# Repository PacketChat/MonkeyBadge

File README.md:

# Monkey Badge

This repository contains the hardware design files, badge code, and backend
infrastructure code for the HushCon Winter 2023 badge.

## badge

The code for the badge is based on [Micropython][1].  For full documentation
read the datasheet, comments, and commit history.

## api-server

The api-server is the backend gameserver it provides an API
interface for the badge to save state and complete challenges.

You will need a redis server with the json mod, `docker run -d -p 6379:6379
redislabs/redismod` works fine.

This is based on FastAPI and is easily executed with: `cd api-server; python3
api-server`

## scoreboard

Built, with Flask

<!--
vim: ts=2 sw=2 tw=80 syntax=md
!-->

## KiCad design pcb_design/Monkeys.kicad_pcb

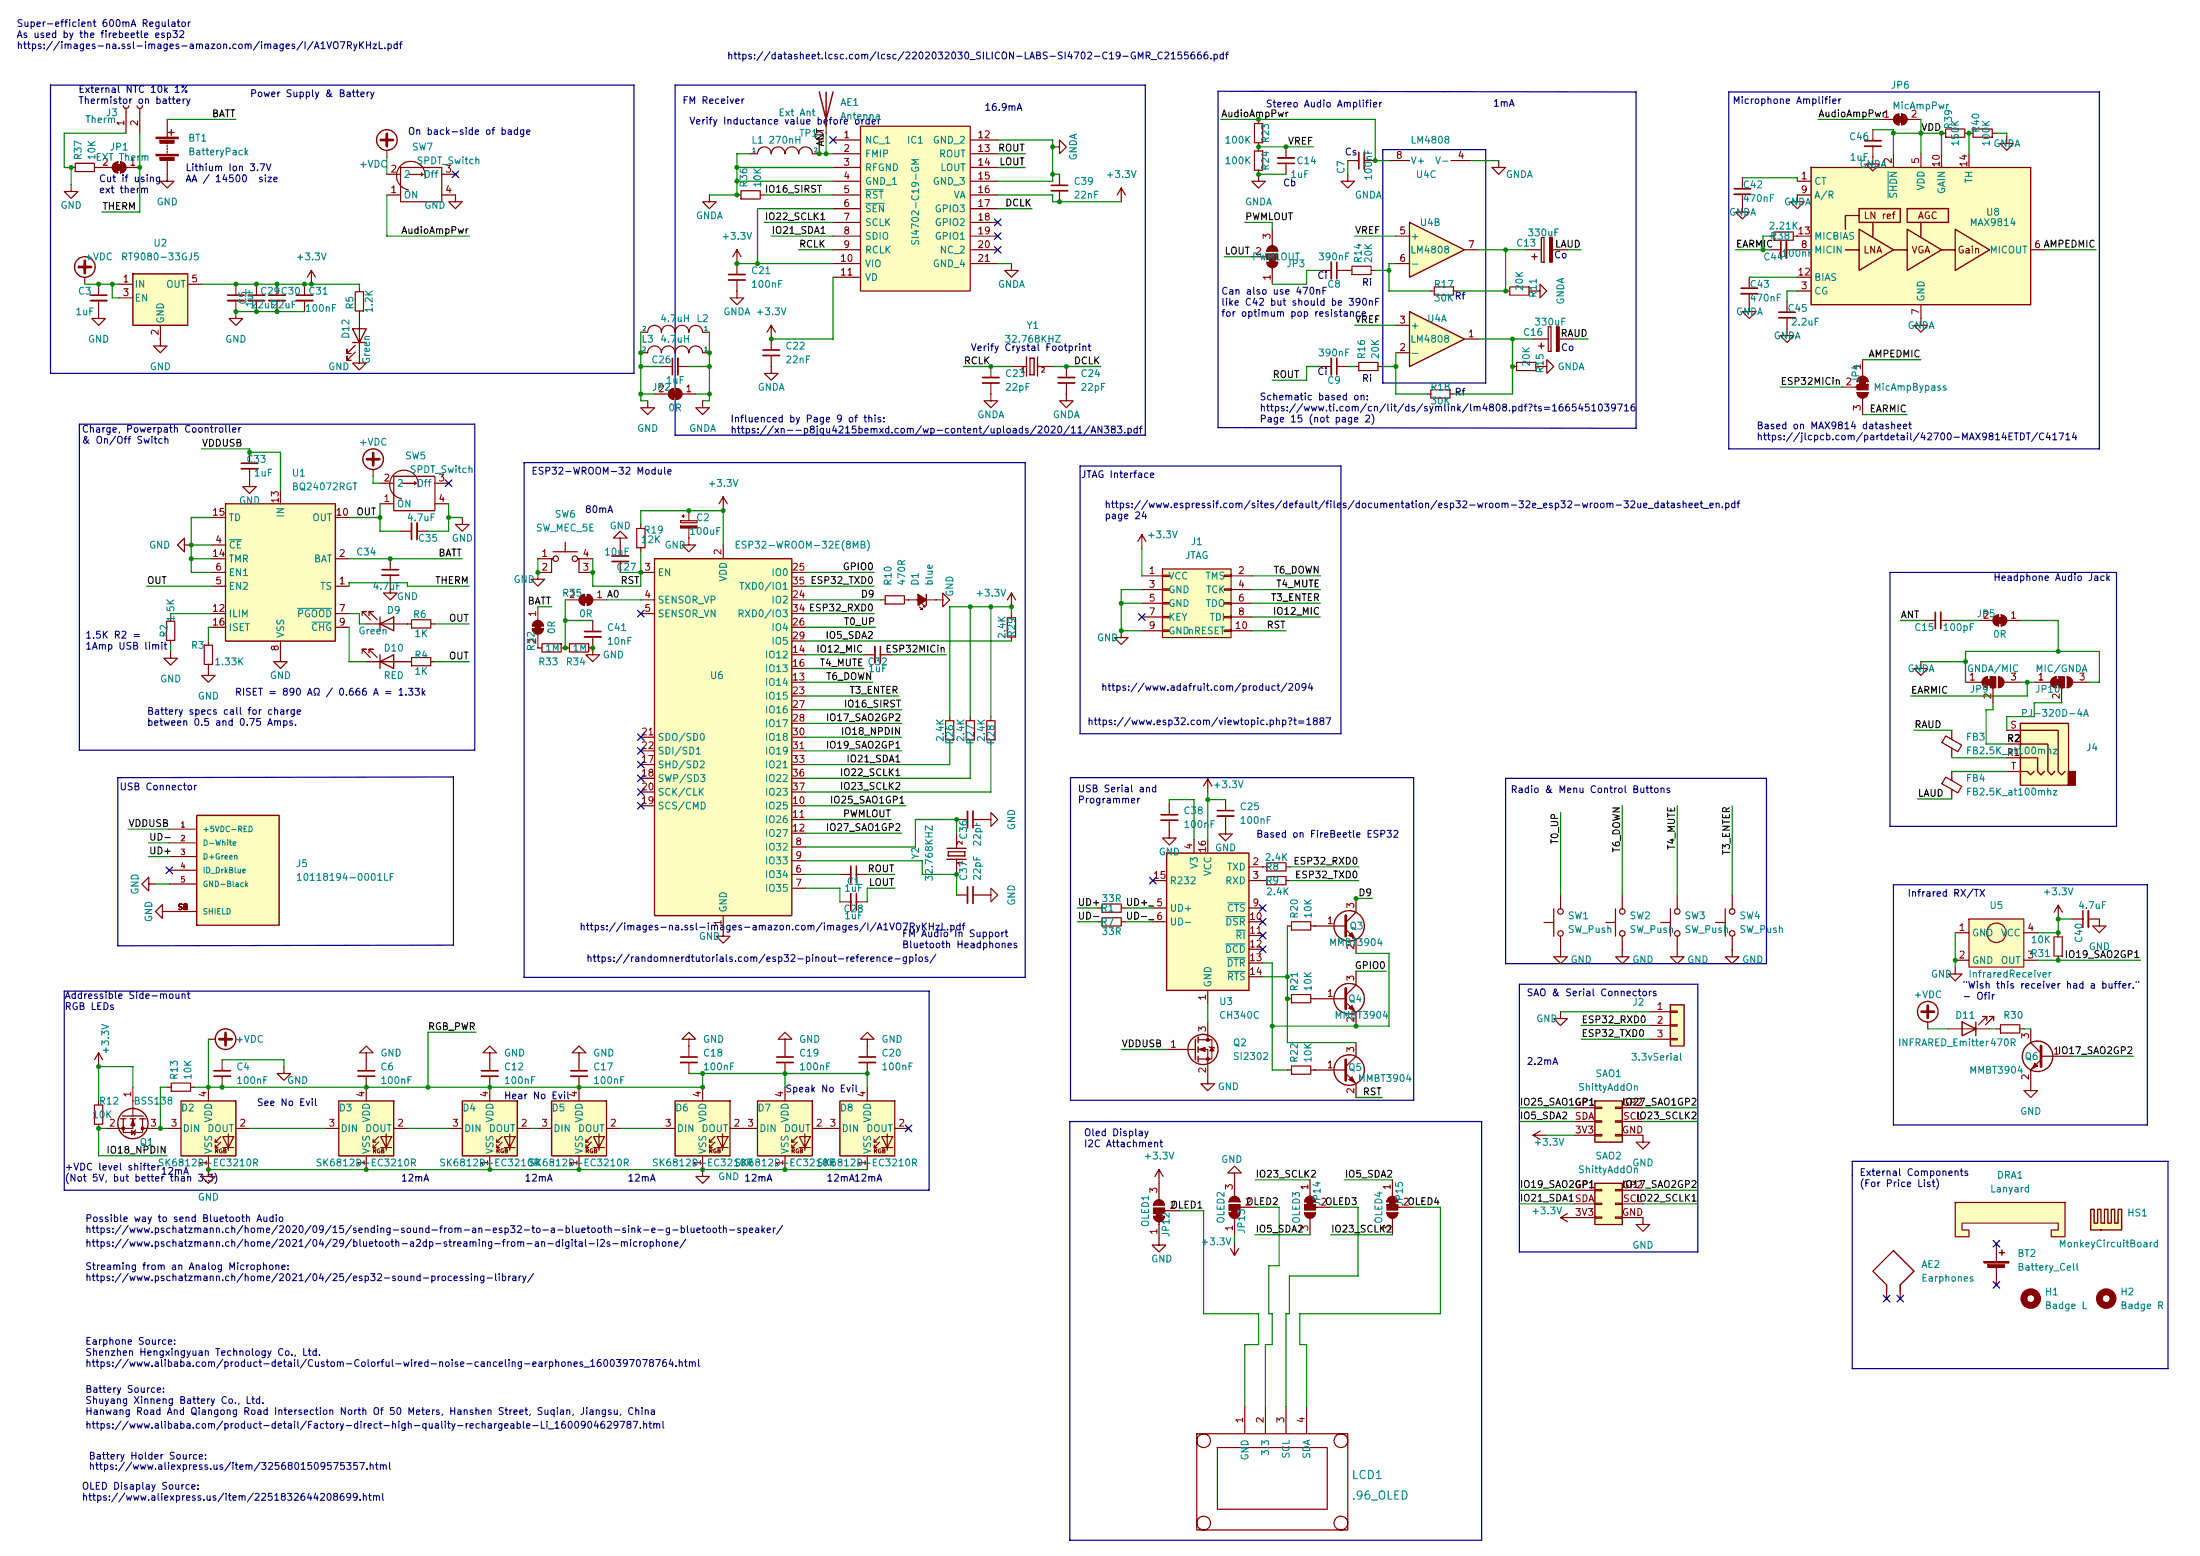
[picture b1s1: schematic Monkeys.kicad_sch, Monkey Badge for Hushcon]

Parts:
AE1: Antenna; Manufacturer_Part_Number DNP; JLCPCB Part #（optional) DNP
AE2: Earphones; Manufacturer_Part_Number DNP; JLCPCB Part #（optional) DNP
BT1: BatteryPack; 1xAA_NUB; Manufacturer_Part_Number DNP; JLCPCB Part #（optional) DNP
BT2: Battery_Cell; Manufacturer_Part_Number DNP; JLCPCB Part #（optional) DNP
C1, C3, C5, C14, C26, C28, C32, C46: 1uF; C_0402_1005Metric; Manufacturer_Part_Number CC0402KRX5R6BB105; JLCPCB Part #（optional) C106254
C2: 100uF; CP_EIA-6032-20_AVX-F; Manufacturer_Part_Number TAJC107K010RNJ; JLCPCB Part #（optional) C8649
C4, C6, C7, C12, C17, C18, C19, C20, C21, C25, C31, C38, C44: 100nF; C_0402_1005Metric; Manufacturer_Part_Number CL05B104KB54PNC; JLCPCB Part #（optional) C307331
C8, C9: 390nF; C_0402_1005Metric; Manufacturer_Part_Number GRM155R61A394KE15D; JLCPCB Part #（optional) C350937
C13, C16: 330uF; CP_EIA-7343-31_Kemet-D; Manufacturer_Part_Number 6TPC330MA; JLCPCB Part #（optional) C558795
C15: 100pF; C_0402_1005Metric; Manufacturer_Part_Number 0402CG101J500NT; JLCPCB Part #（optional) C1546
C22, C39: 22nF; C_0402_1005Metric; Manufacturer_Part_Number 0402B223K500NT; JLCPCB Part #（optional) C1532
C23, C24, C36, C37: 22pF; C_0402_1005Metric; Manufacturer_Part_Number 0402CG220J500NT; JLCPCB Part #（optional) C1555
C27: 10uF; C_0603_1608Metric; Manufacturer_Part_Number CL10A106KP8NNNC; JLCPCB Part #（optional) C19702
C29, C30: 22uF; C_0805_2012Metric; Manufacturer_Part_Number CL21A226MAQNNNE; JLCPCB Part #（optional) C45783
C33: 1uF; C_0805_2012Metric; Manufacturer_Part_Number CC0805KKX7R8BB105; JLCPCB Part #（optional) C91186
C34, C35, C40: 4.7uF; C_0603_1608Metric; Manufacturer_Part_Number CC0603KRX5R6BB475; JLCPCB Part #（optional) C109456
C41: 10nF; C_0402_1005Metric; Manufacturer_Part_Number CL05B103KB5NNNC; JLCPCB Part #（optional) C15195
C42, C43: 470nF; C_0402_1005Metric; Manufacturer_Part_Number C1005X5R474KDTS; JLCPCB Part #（optional) C147712
C45: 2.2uF; C_0402_1005Metric; Manufacturer_Part_Number LMK105ABJ225MVHF; JLCPCB Part #（optional) C386041
D1: blue; LED_0402_1005Metric; Manufacturer_Part_Number TJ-S1005SW4TGLC6B-A5; JLCPCB Part #（optional) C273603
D2, D3, D4, D5, D6, D7, D8: SK6812D-EC3210R; Manufacturer_Part_Number SK6812D-EC3210R; JLCPCB Part #（optional) C2890041
D9, D12: Green; LED_0805_2012Metric; Manufacturer_Part_Number 17-215SYGC/S530-E2/TR8; JLCPCB Part #（optional) C282125
D10: RED; LED_0603_1608Metric; Manufacturer_Part_Number KT-0603R; JLCPCB Part #（optional) C2286
D11: INFRARED_Emitter; LED_1206_3216Metric; Manufacturer_Part_Number MHT153IRCT; JLCPCB Part #（optional) C2764887
DRA1: Lanyard; DNP; Manufacturer_Part_Number DNP; JLCPCB Part #（optional) DNP
FB3, FB4: FB2.5K_at100mhz; C_0603_1608Metric; Manufacturer_Part_Number SZ1608K252CTF; JLCPCB Part #（optional) C316340
H1: Badge L; MountingHole_4.5mm; Manufacturer_Part_Number DNP; JLCPCB Part #（optional) DNP
H2: Badge R; MountingHole_4.5mm; Manufacturer_Part_Number DNP; JLCPCB Part #（optional) DNP
HS1: MonkeyCircuitBoard; DNP; Manufacturer_Part_Number DNP; JLCPCB Part #（optional) DNP
IC1: SI4702-C19-GM; SI4702C19GM; Manufacturer_Part_Number SI4702-C19-GM; JLCPCB Part #（optional) C2155666
J1: JTAG; PinHeader_2x05_P1.27mm_Vertical; Manufacturer_Part_Number DNP; JLCPCB Part #（optional) DNP
J2: 3.3vSerial; PinSocket_1x03_P2.54mm_Vertical; Manufacturer_Part_Number DNP; JLCPCB Part #（optional) DNP
J3: Therm; PinHeader_1x02_P2.54mm_Vertical; Manufacturer_Part_Number DNP; JLCPCB Part #（optional) DNP
J4: PJ-320D-4A; Jack_3.5mm_PJ320D_Horizontal; Manufacturer_Part_Number PJ-320D-4A; JLCPCB Part #（optional) C95562
J5: 10118194-0001LF; AMPHENOL_10118194-0001LF_JT; Manufacturer_Part_Number 10118194-0001LF; JLCPCB Part #（optional) C132563
JP1: EXT Therm; SolderJumper-2_P1.3mm_Bridged_RoundedPad1.0x1.5mm; Manufacturer_Part_Number DNP; JLCPCB Part #（optional) DNP
JP2, JP5: 0R; SolderJumper-2_P1.3mm_Bridged_RoundedPad1.0x1.5mm; Manufacturer_Part_Number DNP; JLCPCB Part #（optional) DNP
JP3: PWMLOUT; SolderJumper-3_P1.3mm_Bridged12_RoundedPad1.0x1.5mm; Manufacturer_Part_Number DNP; JLCPCB Part #（optional) DNP
JP4: MicAmpBypass; SolderJumper-3_P1.3mm_Bridged12_RoundedPad1.0x1.5mm; Manufacturer_Part_Number DNP; JLCPCB Part #（optional) DNP
JP6: MicAmpPwr; SolderJumper-2_P1.3mm_Bridged_RoundedPad1.0x1.5mm
JP9: GNDA/MIC; SolderJumper-3_P1.3mm_Bridged12_RoundedPad1.0x1.5mm; Manufacturer_Part_Number DNP; JLCPCB Part #（optional) DNP
JP10: MIC/GNDA; SolderJumper-3_P1.3mm_Bridged12_RoundedPad1.0x1.5mm; Manufacturer_Part_Number DNP; JLCPCB Part #（optional) DNP
JP12: OLED1; SolderJumper-3_P1.3mm_Bridged12_RoundedPad1.0x1.5mm; Manufacturer_Part_Number DNP; JLCPCB Part #（optional) DNP
JP13: OLED2; SolderJumper-3_P1.3mm_Bridged12_RoundedPad1.0x1.5mm; Manufacturer_Part_Number DNP; JLCPCB Part #（optional) DNP
JP14: OLED3; SolderJumper-3_P1.3mm_Bridged12_RoundedPad1.0x1.5mm; Manufacturer_Part_Number DNP; JLCPCB Part #（optional) DNP
JP15: OLED4; SolderJumper-3_P1.3mm_Bridged12_RoundedPad1.0x1.5mm; Manufacturer_Part_Number DNP; JLCPCB Part #（optional) DNP
L1: 270nH; L_0603_1608Metric_Pad1.05x0.95mm_HandSolder; Manufacturer_Part_Number SCHF160808HR27JT; JLCPCB Part #（optional) C578010
L2, L3: 4.7uH; L_0603_1608Metric_Pad1.05x0.95mm_HandSolder; Manufacturer_Part_Number MLP2012S4R7MT0S1; JLCPCB Part #（optional) C87543
LCD1: .96_OLED; PinHeader_1x04_P2.54mm_Vertical; Manufacturer_Part_Number DNP; JLCPCB Part #（optional) DNP
Q1: BSS138; SOT-323_SC-70; Manufacturer_Part_Number BSS138W-7-F; JLCPCB Part #（optional) C24553
Q2: SI2302; SOT-23; Manufacturer_Part_Number SI2302; JLCPCB Part #（optional) C351399
Q3, Q4, Q5, Q6: MMBT3904; SOT-23; Manufacturer_Part_Number MMBT3904; JLCPCB Part #（optional) C20526
R1, R7: 33R; R_0402_1005Metric; Manufacturer_Part_Number 0402WGF330JTCE; JLCPCB Part #（optional) C25105
R2: 1.5K; R_0805_2012Metric; Manufacturer_Part_Number RC0805FR-071K5L; JLCPCB Part #（optional) C114555
R3: 1.33K; R_0603_1608Metric; Manufacturer_Part_Number RC0603FR-071K33L; JLCPCB Part #（optional) C137778
R4, R6: 1K; R_0805_2012Metric; Manufacturer_Part_Number RC0805JR-071KL; JLCPCB Part #（optional) C100046
R5: 1.2K; R_0805_2012Metric; Manufacturer_Part_Number AR05FTDW1201; JLCPCB Part #（optional) C724883
R8, R9, R26, R27, R28, R29: 2.4K; R_0603_1608Metric; Manufacturer_Part_Number RC0603FR-072K4L; JLCPCB Part #（optional) C114611
R10, R30: 470R; R_0402_1005Metric; Manufacturer_Part_Number 0402WGF4700TCE; JLCPCB Part #（optional) C25117
R11, R14, R15, R16: 20K; R_0402_1005Metric; Manufacturer_Part_Number 0402WGF2002TCE; JLCPCB Part #（optional) C25765
R12, R13, R20, R21, R22, R31, R36, R37: 10K; R_0402_1005Metric; Manufacturer_Part_Number RC0402FR-0710KL; JLCPCB Part #（optional) C60490
R17, R18: 30K; R_0402_1005Metric; Manufacturer_Part_Number RC0402FR-0730KL; JLCPCB Part #（optional) C138008
R19: 12K; R_0402_1005Metric; Manufacturer_Part_Number RC0402FR-0712KL; JLCPCB Part #（optional) C114760
R23, R24, R40: 100K; R_0402_1005Metric; Manufacturer_Part_Number 0402WGF1003TCE; JLCPCB Part #（optional) C25741
R32, R35: 0R; SolderJumper-2_P1.3mm_Bridged_RoundedPad1.0x1.5mm; Manufacturer_Part_Number DNP; JLCPCB Part #（optional) DNP
R33, R34: 1M; R_0402_1005Metric; Manufacturer_Part_Number 0402WGF1004TCE; JLCPCB Part #（optional) C26083
R38: 2.21K; R_0402_1005Metric; Manufacturer_Part_Number NQ02WGF2211TCE; JLCPCB Part #（optional) C270376
R39: 150K; R_0402_1005Metric; Manufacturer_Part_Number AF0402FR-07150KL; JLCPCB Part #（optional) C144033
SAO1, SAO2: ShittyAddOn; ShittyAddOn_Female; Manufacturer_Part_Number DNP; JLCPCB Part #（optional) DNP
SW1, SW2, SW3, SW4: SW_Push; SW_SPST_PTS645; Manufacturer_Part_Number TSA063G50-250; JLCPCB Part #（optional) C294565
SW5, SW7: SPDT_Switch; SPDT Switch MSK12C02-HB; Manufacturer_Part_Number MSK12C02-HB; JLCPCB Part #（optional) C431541
SW6: SW_MEC_5E; Button_metal; Manufacturer_Part_Number TS-1187A-B-A-B; JLCPCB Part #（optional) C318884
TP1: Ext Ant; PinHeader_1x01_P2.54mm_Vertical; Manufacturer_Part_Number DNP; JLCPCB Part #（optional) DNP
U1: BQ24072RGT; VQFN-16-1EP_3x3mm_P0.5mm_EP1.6x1.6mm; Manufacturer_Part_Number BQ24072RGTR; JLCPCB Part #（optional) C140288
U2: RT9080-33GJ5; SOT-23-5; Manufacturer_Part_Number RT9080-33GJ5; JLCPCB Part #（optional) C841192
U3: CH340C; SOIC-16_3.9x9.9mm_P1.27mm; Manufacturer_Part_Number CH340C; JLCPCB Part #（optional) C84681
U4: LM4808; SOIC-8_3.9x4.9mm_P1.27mm; Manufacturer_Part_Number LM4808MX/NOPB; JLCPCB Part #（optional) C141374
U5: InfraredReceiver; IRM-H638T-TR2; Manufacturer_Part_Number IRM-H638T/TR2(DX); JLCPCB Part #（optional) C390031
U6: ESP32-WROOM-32E(8MB); ESP32-WROOM-32; Manufacturer_Part_Number ESP32-WROOM-32E(8MB); JLCPCB Part #（optional) C701342
U8: MAX9814; DFN-14-1EP_3x3mm_P0.4mm_EP1.78x2.35mm; Manufacturer_Part_Number MAX9814ETD+T; JLCPCB Part #（optional) C41714
Y1, Y2: 32.768KHZ; Crystal_SMD_3215-2Pin_3.2x1.5mm; Manufacturer_Part_Number SF32WK32768D31T002; JLCPCB Part #（optional) C271654

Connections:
+3V3: C2.1, C5.1, C21.1, C22.1, C25.1, C29.1, C30.1, C31.1, C39.2, C40.1, IC1.6 (~SEN), IC1.10 (VIO), IC1.11 (VD), IC1.16 (VA), J1.1 (VCC), JP12.3 (B), JP13.1 (A), Q1.1 (G), R5.2, R12.2, R19.2, R26.2, R27.2, R28.2, R29.2, R31.2, SAO1.3V3, SAO2.3V3, U2.5 (OUT), U3.16 (VCC), U5.4 (VCC), U6.2 (VDD)
+VDC: C3.1, C4.2, C6.2, C12.2, C17.2, C18.2, C19.2, C20.2, D2.4 (VDD), D3.4 (VDD), D4.4 (VDD), D5.4 (VDD), D6.4 (VDD), D7.4 (VDD), D8.4 (VDD), D11.2 (A), R13.2, SW5.2, SW7.2, U2.1 (IN), U2.3 (EN)
/A0: R35.1 (A), U6.4 (SENSOR_VP)
/AMPEDMIC: JP4.1 (A), U8.6 (MICOUT)
/ANT: AE1.1, C15.1, IC1.2 (FMIP), L1.2, TP1.1
/AudioAmpPwr: C7.2, JP6.1 (A), R23.1, SW7.1 (ON), U4.8 (V+)
/BATT: BT1.1 (+), C34.1, R32.1 (A), U1.2 (BAT), U1.3 (BAT)
/D9: Q3.3 (C), R10.1, U6.24 (IO2)
/DCLK: C24.1, IC1.17 (GPIO3), Y1.2
/EARMIC: C44.1, JP4.3 (B), JP9.3 (B), JP10.1 (A), R38.1
/ESP32MICin: C32.1, JP4.2 (C)
/ESP32_RXD0: J2.2, R8.2, U6.34 (RXD0/IO3)
/ESP32_TXD0: J2.3, R9.2, U6.35 (TXD0/IO1)
/GPIO0: Q4.3 (C), U6.25 (IO0)
/IO5_SDA2: JP14.3 (B), JP15.1 (A), R29.1, SAO1.SDA, U6.29 (IO5)
/IO12_MIC: C32.2, J1.8 (TDI), U6.14 (IO12)
/IO16_SIRST: IC1.5 (~RST), R36.2, U6.27 (IO16)
/IO17_SAO2GP2: Q6.1 (B), SAO2.GP2 (GPIO2), U6.28 (IO17)
/IO18_NPDIN: Q1.2 (S), R12.1, U6.30 (IO18)
/IO19_SAO2GP1: R31.1, SAO2.GP1 (GPIO1), U5.3 (OUT), U6.31 (IO19)
/IO21_SDA1: IC1.8 (SDIO), R26.1, SAO2.SDA, U6.33 (IO21)
/IO22_SCLK1: IC1.7 (SCLK), R27.1, SAO2.SCL, U6.36 (IO22)
/IO23_SCLK2: JP14.1 (A), JP15.3 (B), R28.1, SAO1.SCL, U6.37 (IO23)
/IO25_SAO1GP1: SAO1.GP1 (GPIO1), U6.10 (IO25)
/IO27_SAO1GP2: SAO1.GP2 (GPIO2), U6.12 (IO27)
/LAUD: C13.2, FB4.2
/LOUT: C28.1, IC1.14 (LOUT), JP3.2 (C)
/OLED1: JP12.2 (C), LCD1.1 (GND)
/OLED2: JP13.2 (C), LCD1.2 (3.3)
/OLED3: JP14.2 (C), LCD1.3 (SCL)
/OLED4: JP15.2 (C), LCD1.4 (SDA)
/OUT: C35.1, R4.2, R6.2, SW5.1 (ON), U1.5 (EN2), U1.10 (OUT), U1.11 (OUT)
/PWMLOUT: JP3.3 (B), U6.11 (IO26)
/R2: J4.R2, JP9.2 (C)
/RAUD: C16.2, FB3.1
/RCLK: C23.1, IC1.9 (RCLK), Y1.1
/ROUT: C1.1, C9.2, IC1.13 (ROUT)
/RST: C27.1, J1.10 (nRESET), Q5.2 (E), R19.1, SW6.3 (K), SW6.4 (A), U6.3 (EN)
/T0_UP: SW1.2, U6.26 (IO4)
/T3_ENTER: J1.6 (TDO), SW4.2, U6.23 (IO15)
/T4_MUTE: J1.4 (TCK), SW3.2, U6.16 (IO13)
/T6_DOWN: J1.2 (TMS), SW2.2, U6.13 (IO14)
/THERM: J3.2, JP1.1 (A), U1.1 (TS)
/UD+: J5.3 (D+Green), R1.1
/UD+_: R1.2, U3.5 (UD+)
/UD-: J5.2 (D-White), R7.1
/UD-_: R7.2, U3.6 (UD-)
/VDD: C46.1, JP6.2 (B), R39.1, U8.2 (~SHDN), U8.5 (VDD), U8.10 (GAIN)
/VDDUSB: C33.1, J5.1 (+5VDC-RED), Q2.1 (G), U1.13 (IN)
/VREF: C14.2, R23.2, R24.1, U4.3 (+), U4.5 (+)
GND: BT1.2 (-), C2.2, C3.2, C4.1, C5.2, C6.1, C12.1, C17.1, C18.1, C19.1, C20.1, C25.2, C26.1, C27.2, C29.2, C30.2, C31.2, C33.2, C34.2, C35.2, C36.2, C37.2, C38.2, C40.2, C41.2, D1.1 (K), D2.1 (VSS), D3.1 (VSS), D4.1 (VSS), D5.1 (VSS), D6.1 (VSS), D7.1 (VSS), D8.1 (VSS), D12.1 (K), J1.3 (GND), J1.5 (GND), J1.9 (GND), J2.1, J3.1, J5.5 (GND-Black), J5.S1 (SHIELD), J5.S2 (SHIELD), J5.S3 (SHIELD), J5.S4 (SHIELD), J5.S5 (SHIELD), J5.S6 (SHIELD), JP2.2 (B), JP12.1 (A), JP13.3 (B), L2.2, L3.2, Q2.2 (S), Q6.2 (E), R2.1, R3.2, R34.1, R37.1, SAO1.GND, SAO2.GND, SW1.1, SW2.1, SW3.1, SW4.1, SW5.4, SW6.1, SW6.2, SW7.4, U1.4 (~CE), U1.6 (EN1), U1.8 (VSS), U1.14 (TMR), U1.15 (TD), U1.17 (VSS), U2.2 (GND), U5.1 (GND), U5.2 (GND), U6.1 (GND), U6.15 (GND), U6.38 (GND), U6.39 (GND)
GNDA: C7.1, C14.1, C21.2, C22.2, C23.2, C24.2, C26.2, C39.1, C42.2, C43.2, C45.2, C46.2, IC1.3 (RFGND), IC1.4 (GND_1), IC1.12 (GND_2), IC1.15 (GND_3), IC1.21 (GND_4), JP2.1 (A), JP5.1 (A), JP9.1 (A), JP10.3 (B), L1.1, L2.1, L3.1, R11.1, R15.1, R24.2, R36.1, R40.1, U4.4 (V-), U8.4 (GND), U8.7 (GND), U8.9 (A/R), U8.11 (GND), U8.15 (GND)
unnamed: C1.2, U6.6 (IO34)
unnamed: C8.1, R14.1
unnamed: C8.2, JP3.1 (A)
unnamed: C9.1, R16.1
unnamed: C13.1, R11.2, R17.1, U4.7
unnamed: C15.2, JP5.2 (B)
unnamed: C16.1, R15.2, R18.1, U4.1
unnamed: C28.2, U6.7 (IO35)
unnamed: C36.1, U6.8 (IO32), Y2.2
unnamed: C37.1, U6.9 (IO33), Y2.1
unnamed: C38.1, U3.4 (V3)
unnamed: C41.1, R33.1, R34.2, R35.2 (B)
unnamed: C42.1, U8.1 (CT)
unnamed: C43.1, U8.12 (BIAS)
unnamed: C44.2, U8.8 (MICIN)
unnamed: C45.1, U8.3 (CG)
unnamed: D1.2 (A), R10.2
unnamed: D2.2 (DOUT), D3.3 (DIN)
unnamed: D2.3 (DIN), Q1.3 (D), R13.1
unnamed: D3.2 (DOUT), D4.3 (DIN)
unnamed: D4.2 (DOUT), D5.3 (DIN)
unnamed: D5.2 (DOUT), D6.3 (DIN)
unnamed: D6.2 (DOUT), D7.3 (DIN)
unnamed: D7.2 (DOUT), D8.3 (DIN)
unnamed: D9.1 (K), U1.7 (~PGOOD)
unnamed: D9.2 (A), R6.1
unnamed: D10.1 (K), U1.9 (~CHG)
unnamed: D10.2 (A), R4.1
unnamed: D11.1 (K), R30.1
unnamed: D12.2 (A), R5.1
unnamed: FB3.2, J4.R1
unnamed: FB4.1, J4.T
unnamed: J4.S, JP10.2 (C)
unnamed: JP1.2 (B), R37.2
unnamed: Q2.3 (D), U3.1 (GND)
unnamed: Q3.1 (B), R20.2
unnamed: Q3.2 (E), Q4.2 (E), R22.1, U3.13 (~DTR)
unnamed: Q4.1 (B), R21.2
unnamed: Q5.1 (B), R22.2
unnamed: Q5.3 (C), R20.1, R21.1, U3.14 (~RTS)
unnamed: Q6.3 (C), R30.2
unnamed: R2.2, U1.12 (ILIM)
unnamed: R3.1, U1.16 (ISET)
unnamed: R8.1, U3.2 (TXD)
unnamed: R9.1, U3.3 (RXD)
unnamed: R14.2, R17.2, U4.6 (-)
unnamed: R16.2, R18.2, U4.2 (-)
unnamed: R32.2 (B), R33.2
unnamed: R38.2, U8.13 (MICBIAS)
unnamed: R39.2, R40.2, U8.14 (TH)

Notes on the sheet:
See No Evil
Can also use 470nF like C42 but should be 390nF for optimum pop resistance
https://www.alibaba.com/product-detail/Factory-direct-high-quality-rechargeable-Li_1600904629787.html
Addressible Side-mount RGB LEDs
Battery specs call for charge between 0.5 and 0.75 Amps.
https://www.aliexpress.us/item/3256801509575357.html
12mA
Speak No Evil
https://datasheet.lcsc.com/lcsc/2202032030_SILICON-LABS-SI4702-C19-GMR_C2155666.pdf
On back-side of badge
"Wish this receiver had a buffer." - Ofir
Radio & Menu Control Buttons
https://randomnerdtutorials.com/esp32-pinout-reference-gpios/
Verify Inductance value before order
https://www.esp32.com/viewtopic.php?t=1887
1.5K R2 = 1Amp USB limit
https://www.pschatzmann.ch/home/2021/04/29/bluetooth-a2dp-streaming-from-an-digital-i2s-microphone/
+VDC level shifter (Not 5V, but better than 3.3)
Streaming from an Analog Microphone: https://www.pschatzmann.ch/home/2021/04/25/esp32-sound-processing-library/
Earphone Source: Shenzhen Hengxingyuan Technology Co., Ltd. https://www.alibaba.com/product-detail/Custom-Colorful-wired-noise-canceling-earphones_1600397078764.html
Based on FireBeetle ESP32
https://www.espressif.com/sites/default/files/documentation/esp32-wroom-32e_esp32-wroom-32ue_datasheet_en.pdf page 24
Cut if using ext therm
https://www.adafruit.com/product/2094
Stereo Audio Amplifier
Oled Display I2C Attachment
OLED Disaplay Source: https://www.aliexpress.us/item/2251832644208699.html
External Components (For Price List)
Headphone Audio Jack
Battery Source: Shuyang Xinneng Battery Co., Ltd. Hanwang Road And Qiangong Road Intersection North Of 50 Meters, Hanshen Street, Suqian, Jiangsu, China
https://images-na.ssl-images-amazon.com/images/I/A1VO7RyKHzL.pdf
SAO & Serial Connectors
Based on MAX9814 datasheet https://jlcpcb.com/partdetail/42700-MAX9814ETDT/C41714
Battery Holder Source:
RISET = 890 AΩ / 0.666 A = 1.33k
FM Audio In Support Bluetooth Headphones
Power Supply & Battery
2.2mA
Possible way to send Bluetooth Audio https://www.pschatzmann.ch/home/2020/09/15/sending-sound-from-an-esp32-to-a-bluetooth-sink-e-g-bluetooth-speaker/
Infrared RX/TX

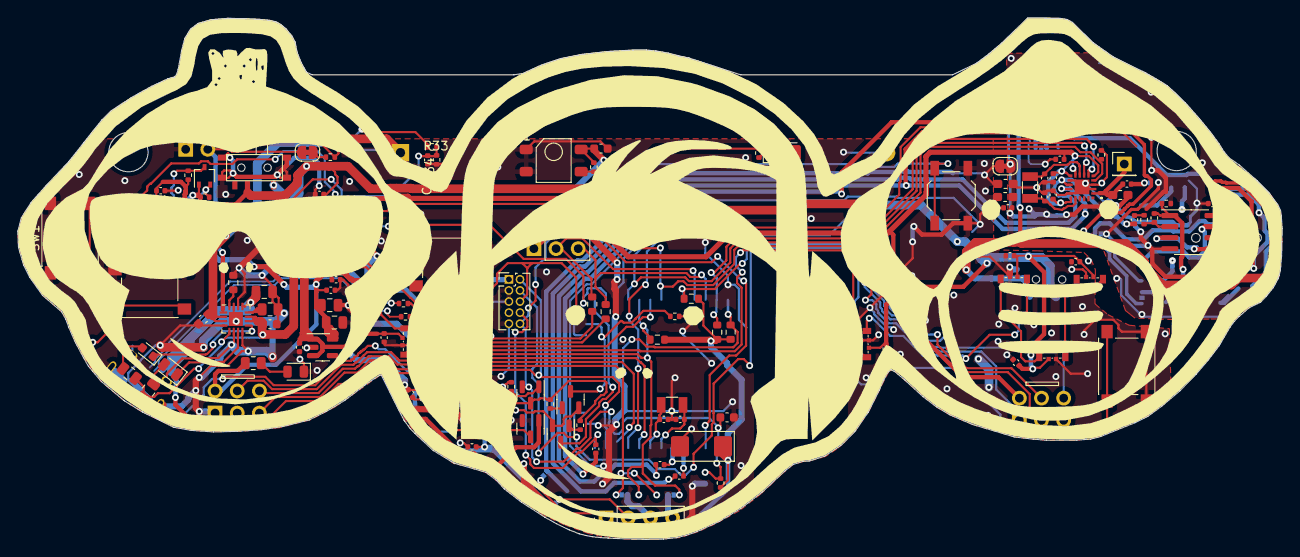
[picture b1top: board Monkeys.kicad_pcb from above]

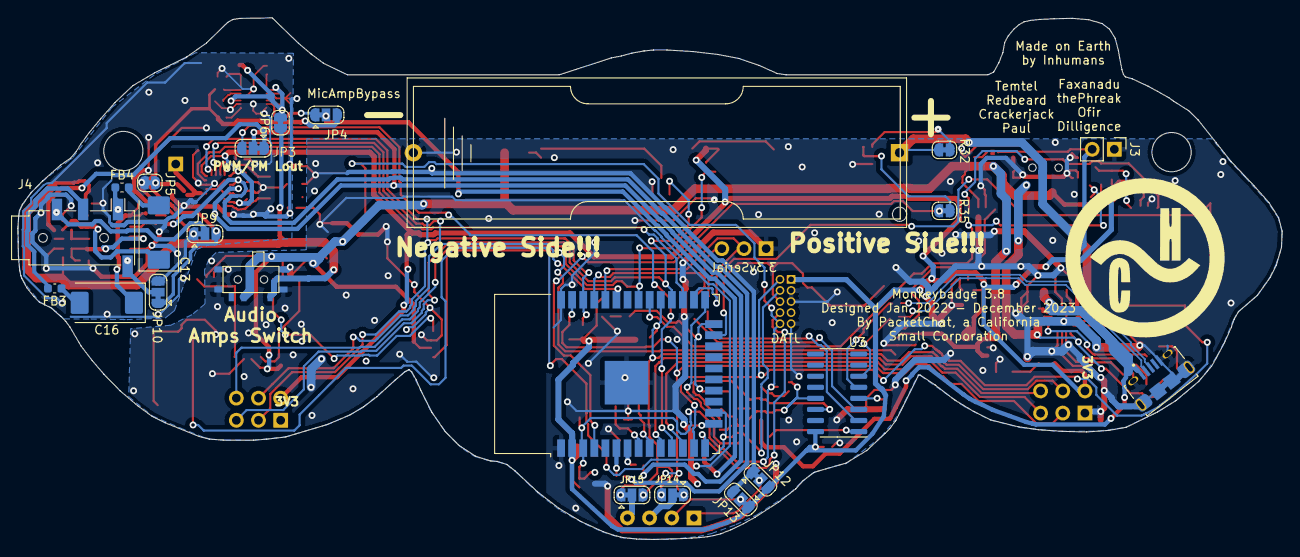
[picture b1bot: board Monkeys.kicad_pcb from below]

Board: 2 copper layers, 144.9 x 59.8 mm, 147 parts (23 on the bottom side), 102 nets.

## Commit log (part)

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2023-09-16 brb: Adding some monkeybadge scripts
    This is a collection of initial scripts for the monkeybadge, including
    the hal.
    This is just a point in time snapshot. Longer term this lives as a part
    of the monkey badge repository itself.
2023-09-20 Added simple IR test scripts for sending and receiving.
2023-09-25 This loosy goosy method of decoding works now.
2023-10-13 inital but broken
2023-10-17 pushing some of my code up finally
2023-10-25 updating api server
2023-10-31 menu fixes
2023-11-12 scoreboard empty dir
2023-11-14 chore: Add frozen MicroPython to .gitignore
    The MPY optimized files for MicroPython are automatically optimized in
    the process of building them into the firmware. This should help in
    accurately establishing the size of the code for the purpose of ensuring
    OTA updates continue to work.
2023-11-15 scoreboard and badge changes
2023-11-15 removed redis module utilization
2023-11-17 Added predator and boot sequence light routines.
2023-11-18 more robust display api
2023-11-19 change monkeybadge display to use display api
2023-11-21 small ticker and monkeybadge fixes
2023-11-21 some small fixes
2023-11-22 some monkeybadge changes
2023-11-22 chore: Adding a build action for the badge firmware
    This is a basic scaffolding of the use of GitHub actions to monitor the
    repository for changes to the badge firmware and or the board
    definition.
    As of right now there are five core actions:
    - Check out the repository
    - Check out MicroPython
2023-11-27 sync code
2023-11-28 recent changes
2023-11-29 bug: SI470X method rename (set_volume)
    In a prior update to the MonkeyBadge class the method set_volume was
    renamed to setVolume(). This was discovered when performing a manual
    audit of the code base, as can be seen below:
    ```
    >>> b.radio.changeVolume(12)
    Traceback (most recent call last):
2023-11-30 better errorhandling for the btree database connections
2023-11-30 feature: refactor led library
    removed the demo function - it's not used
    run led playback via asyncio
2023-11-30 chore: refactor wifi library
    moved `get_mac()` out of the WifiManager class
    removed asynchio
    simplified init.
2023-11-30 feature: added IR matching api endpoints
    Added 2 new endpoints for IR matching.
    - friendrequest: checks to see if the IRID submitted is in the redis datastore.
    if the IRID exists, the server will add the badgehandle and uuid of the remote
    badge to the matches list.
    - getIRID: generates a unique IRID (16bit) address, saves it to the redis datastore
    as a key/value pair (IRID:UUID), also adds to the game state for UUID.
2023-11-30 chore: reduce scope of the build
    This adds the ability to manually call dispatch a build via
    `workflow_call` option in GitHub Actions.
    Additionally we're removing the "push" targets for everything except
    this file. Now build should be triggered based on PRs against the
    branch `main`.
2023-12-01 Revert "chore: Adding the Python linter `ruff` (#33)"
    This reverts commit 3fc2a28e658ce7aec82d71c8463d57b47ebf5031.
2023-12-01 move off of the self-hosted runner (#39)
    * move off of the self-hosted runner
    We should move this off of the self hosted running. This job should
    spawn and run quickly.
    * typo: workflow_dispatch not workflow_call
2023-12-02 chore: formatting + fixing ota urls in monkeybadge
    boot.py - had a spelling error
    db.py - formatting and ignore for linter
    gameclient.py - removed unused modules and changed None to return None.
    monkeybadge.py - removed unused modules, formatting.
2023-12-02 BUG: api-server registration bug with token.
    fixed a logic bug with returning the token to the client in the register function.
2023-12-02 chore: refactoring missing bits from working_sync branch
2023-12-02 chore: api-server refactor
    api-server generates an IRID during registration instead of
    a seperate call.
2023-12-02 fix some linter errors (#43)
    * fix some linter errors
    * remove pin reference from tx init
2023-12-02 nit: Removing unused `err` in Exception (#45)
    In `badge/library/monkeybadge.py` there was a single unused `err`
    variable which was not caught in other linting change sets.
2023-12-02 feature: Battery Meter (#48)
    Adding a class for measuring the battery life. The `Meter` class
    contains an `info()` method that calculates the battery life based on the
    measurement returned of the ADC reading. The math is a little weird
    because I had to average it on various batteries and there's a voltage
    divider that gives me only 2.4V to measure.
    Changes:
2023-12-02 fmt: Ruff mass re-formatting
    In order to live in a world filled with less eye stabby code, the full
    code base has been run through the tool `ruff`.
    The result of this is the first fully untouched run of `ruff`.
2023-12-02 feature: SHA hash of running partition (#51)
    This adds a new method "check_self_sha" to the OTA object. From there
    this method is utilized when checking verifying the desired versus
    expected firmware state as expressed via JSON metadata.
    If the hash of the running firmware matches the hash as provided by the
    remote server there's not even a point in downloading the binary file.
2023-12-03 feature: OLED brightness controls (#52)
    * feature: OLED brightness controls
    Adding a menu item with a helper function to set the OLED brightness
    globally. These settings are contrast values ranging from 1-255. Three
    settings exist for setting the contrast to low, medium and high which
    set it to 1, 80 and 200 respectively.
    I also added a default contrast setting of 1, so that when the badge
2023-12-03 Reformat with ruff
2023-12-03 ruff formatting
2023-12-03 fix: Removing unused menu items. (#57)
    Removed the LED Brightness global setting menu since we're not setting
    that. Also removed the Debounce menu.
    Tested on the badge with the latest firmware, good to go.
2023-12-03 Add sponsors menu in the about menu (#55)
    * Add sponsors menu in the about menu
    * added sponsors menu with sponsors
    * also added temsgurl to credits
    * ruff formatting
2023-12-04 feature: Random list of 5 lightshows for menu
    This doesn't work yet, checking in to see if someone can review and tell
    me if I'm going in the right direction.
    Thanks.
2023-12-04 Add a challenge status menu item (#61)
    * Add a challenge status menu item
    * ruff format
    * Fix small bug in challenge2 display
    * correct typo from challenge1 to challenge2
2023-12-04 add missing ir_tx lib and update update.sh
2023-12-04 fix import error in boot.py
2023-12-04 hardware: Badge revision 3.5
    In this revision changes were made to the following components:
    - Stereo amplifier
    - Microphone amplifier
    - Addition of a JTAG port
    This spin of the hardware went to initial manufacturing with the gerbers
    provided on August 30th, 2023.
2023-12-04 hardware: Badge revision 3.7
    In this revision changes were made to the following components:
    - Change C42 in stereo amplifier from 470nF to 390nF
    - Changed JP4 default state (Microphone amplifier - disabled amp by
    default)
    This spin of the hardware went to initial manufacturing with the gerbers
    provided on September 15th, 2023.
2023-12-04 feature: Added all LED light shows
    Added a dictionary `lightshow_dict` to `library/leds.py` to store a key
    value pair for each light show function and a friendly name. Then I
    initialized an empty list `selected_lightshows` to store 5 random
    light shows to be displayed in the menu. Added a helper function
    `selected_lightshows()` that returns the list. I also refactored any
    light show that took parameters and internalized all the values within
2023-12-05 fix: Removing unused getter and appending menu
    Changes made based on comments in PR.
    Removed an unused getter from library/leds.py.
    Changed the menu generation from extend to append becaues it's the
    proper way to do it.
2023-12-05 Add sender info to timed message, auto-format
    * auto-format through ruff
    * add sender information to timed message on emote
2023-12-05 Add emote functionality (#68)
    * Add emote functionality
    * added list of emotes in config
    * fix send_emote function in ir lib to remove dst
    * add emote submenu in social menu
    * populate emote submenu with emotes from config
    * add EMOTE ir packet handler in infrared_check
2023-12-05 Small bugfix + stubs (#69)
    * Fix small bug in IR library
    * because monkeys/hidden objects use the addr field as a secret code
    if any badge had the same id it would ignore those codes
    this fixes that issue by making sure not to ignore any
    of the monkey/hidden object codes
    * Add stubs for hidden objects and monkey reactions
2023-12-05 Change extra bytes on MONKEY/HIDDEN_OBJECT opcodes (#71)
    * change the extra bytes field from 2 to 0
2023-12-05 bug: fixed scoreboard failing to load
    there are multiple types of keys in redis now,
    I built a simple function that validates the key
    is a proper uuid (in this case a hyphen deliminated mac addr)
2023-12-06 feature: monkey mode on api-server
    turn on and off monkeymode for any badge:
    POST `http://apiserver/monkeymode`
    with the request body:
    ```
    {
    "key": "THECONFIGUREDADMINKEY",
2023-12-06 feature: Added light shows to thank the badge team
    Added 8 light shows to represent the badge team. Also cleaned up
    superflous comments.
    - Ran ruff check and format.
    - Tested all 30 lightshows, the new light shows are performant and
    don't have much interfearance when the badge is checking in.
    - Adjusted some comments in the previous light shows to clean up
2023-12-06 feature: implementing hiddenobject and monkey discovery (#78)
    feature: implementing hiddenobject and monkey discovery in gameclient/monkeybadge.
    api-server/main.py:
    - added checks to see if uber and monkey badges were already interacted with
    changed return codes to 208 (already reported) instead of 400.
    badge/monkeybadge.py:
    - added handling for hiddenobject and monkeymode badge (monkeysee)
2023-12-07 feature: Battery charge warning message (#79)
    * feature: Battery charge warning message
    Added a small power check in the main controller. I figured this is
    where you should put this since it's so important.
    The power level is first stored, then sliced and the whole integer is
    used as the threshold, currently set to `5`. The power meter's range is
    definitely safe enough to go lower, but just in case some batteries
2023-12-08 bug: Display message about update on boot (#81)
    To avoid any confusion about wondering what the badge is doing we are
    displaying a message about performing an over the air update to the
    SSD1306 display when occurring.
2023-12-08 feature: badge_cli
    commented out gameclient print statements
    changed monkeybadge print statement to logger
    badge_cli adds several features to interact with the badge.
    recovery of API tokens
    factory reset
    fixing linting error
2023-12-08 nit: Remove spurious comment
    This removes a TODO comment because the work has been completed.
2023-12-08 feature: made the challenge2/3 requests queued.
    In case wifi is not working at the time the challenge is completed
    the call will queue.
    monkeyseerequest and hiddenobjectrequest.
2023-12-08 feature: Added confirmation logic for ota reset (#85)
    This code implements a confirmation dialogue.
    fixing merge conflict
2023-12-08 turned on boot lightshow
2023-12-08 updated styling for scoreboard so it can be viewed on the projector
2023-12-08 fixing again
2023-12-09 feature: rate limiting for ch2/3 (#93)
    due to rampant abuse in ch1, I have implemented rate limiting in the remaining
    challenges. :evilgrin:

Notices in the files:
hardware/Monkeys.kicad_sch:
Copyright PacketChat
pcb_design/Monkeys.kicad_pcb:
Copyright 2023 PacketChat
